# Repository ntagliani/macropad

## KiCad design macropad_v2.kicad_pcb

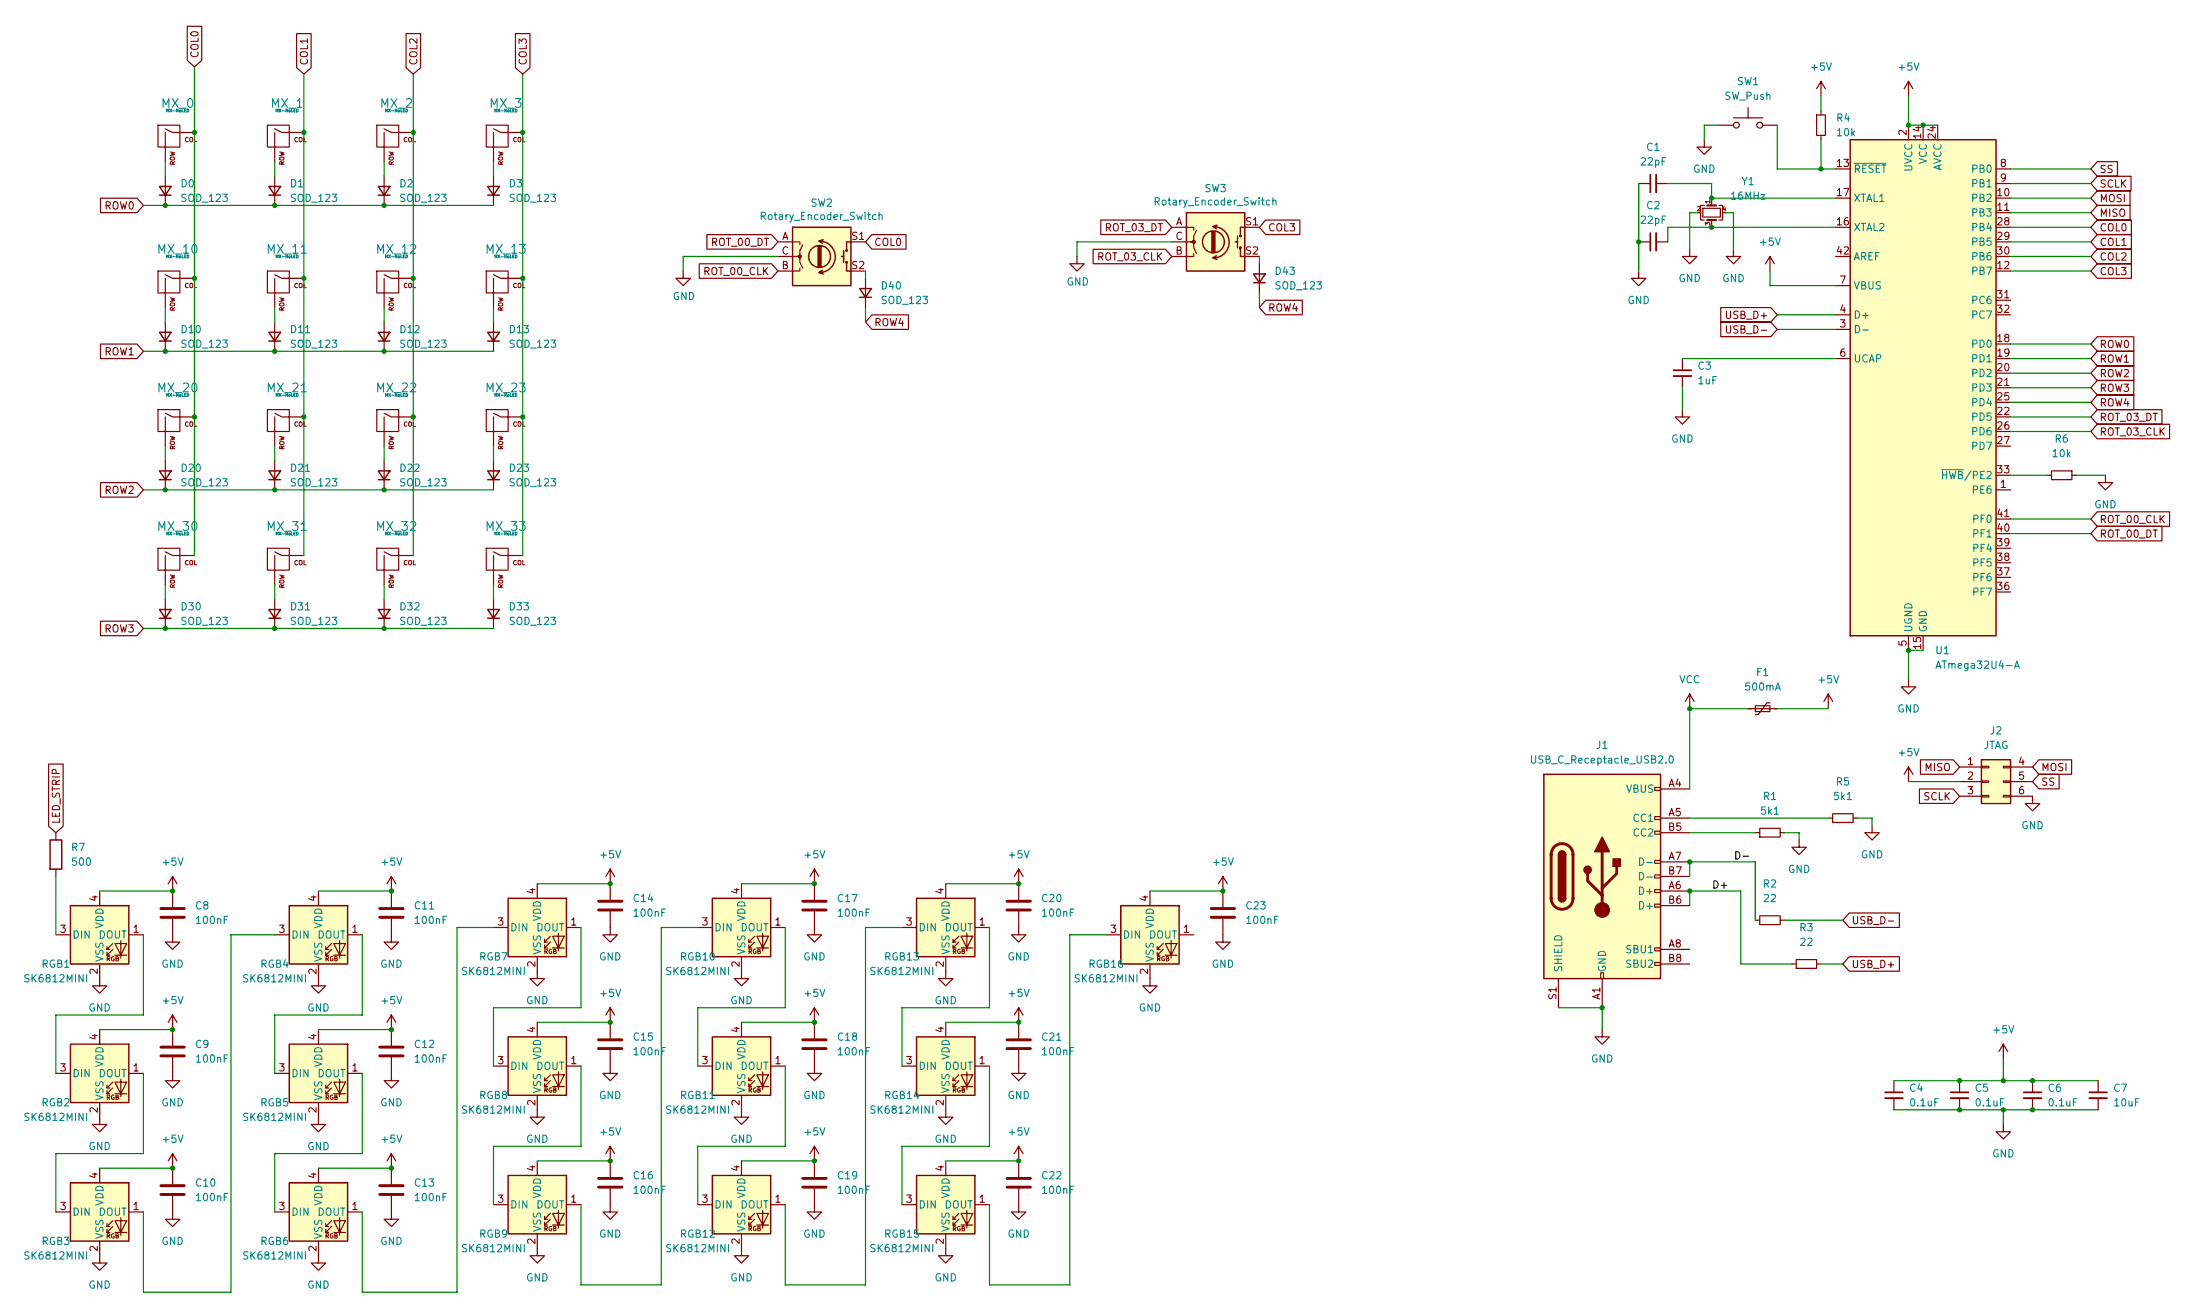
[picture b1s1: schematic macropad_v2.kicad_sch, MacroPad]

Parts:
C1, C2: 22pF; C_0805_2012Metric
C3: 1uF; C_0805_2012Metric
C4, C5, C6: 0.1uF; C_0805_2012Metric
C7: 10uF; C_0805_2012Metric
C8, C9, C10, C11, C12, C13, C14, C15, C16, C17, C18, C19, C20, C21, C22, C23: 100nF; C_0805_2012Metric
D0, D1, D2, D3, D10, D11, D12, D13, D20, D21, D22, D23, D30, D31, D32, D33, D40, D43: SOD_123; D_0805_2012Metric
F1: 500mA; Fuse_0805_2012Metric
J1: USB_C_Receptacle_USB2.0; USB_C_Receptacle_HRO_TYPE-C-31-M-12
J2: JTAG; Reset_Pretty
MX_0, MX_1, MX_2, MX_3, MX_10, MX_11, MX_12, MX_13, MX_20, MX_21, MX_22, MX_23, MX_30, MX_31, MX_32, MX_33: MX-NoLED; SW_Cherry_MX_1.00u_Plate
R1, R5: 5k1; R_0805_2012Metric
R2, R3: 22; R_0805_2012Metric
R4, R6: 10k; R_0805_2012Metric
R7: 500; R_0805_2012Metric
RGB1, RGB2, RGB3, RGB4, RGB5, RGB6, RGB7, RGB8, RGB9, RGB10, RGB11, RGB12, RGB13, RGB14, RGB15, RGB16: SK6812MINI; LED_SK6812MINI_PLCC4_3.5x3.5mm_P1.75mm
SW1: SW_Push; Reset_Pretty
SW2, SW3: Rotary_Encoder_Switch; RotaryEncoder_Alps_EC11E-Switch_Vertical_H20mm
U1: ATmega32U4-A; TQFP-44_10x10mm_P0.8mm
Y1: 16MHz; Crystal_SMD_3225-4Pin_3.2x2.5mm

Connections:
+5V: C4.1, C5.1, C6.1, C7.1, C8.1, C9.1, C10.1, C11.1, C12.1, C13.1, C14.1, C15.1, C16.1, C17.1, C18.1, C19.1, C20.1, C21.1, C22.1, C23.1, F1.2, J2.2, R4.1, RGB1.4 (VDD), RGB2.4 (VDD), RGB3.4 (VDD), RGB4.4 (VDD), RGB5.4 (VDD), RGB6.4 (VDD), RGB7.4 (VDD), RGB8.4 (VDD), RGB9.4 (VDD), RGB10.4 (VDD), RGB11.4 (VDD), RGB12.4 (VDD), RGB13.4 (VDD), RGB14.4 (VDD), RGB15.4 (VDD), RGB16.4 (VDD), U1.2 (UVCC), U1.7 (VBUS), U1.14 (VCC), U1.24 (AVCC), U1.34 (VCC), U1.44 (AVCC)
/D+: J1.A6 (D+), J1.B6 (D+), R3.1
/D-: J1.A7 (D-), J1.B7 (D-), R2.1
COL0: MX_0.1 (COL), MX_10.1 (COL), MX_20.1 (COL), MX_30.1 (COL), SW2.S1, U1.28 (PB4)
COL1: MX_1.1 (COL), MX_11.1 (COL), MX_21.1 (COL), MX_31.1 (COL), U1.29 (PB5)
COL2: MX_2.1 (COL), MX_12.1 (COL), MX_22.1 (COL), MX_32.1 (COL), U1.30 (PB6)
COL3: MX_3.1 (COL), MX_13.1 (COL), MX_23.1 (COL), MX_33.1 (COL), SW3.S1, U1.12 (PB7)
GND: C1.1, C2.1, C3.2, C4.2, C5.2, C6.2, C7.2, C8.2, C9.2, C10.2, C11.2, C12.2, C13.2, C14.2, C15.2, C16.2, C17.2, C18.2, C19.2, C20.2, C21.2, C22.2, C23.2, J1.A1 (GND), J1.A12 (GND), J1.B1 (GND), J1.B12 (GND), J1.S1 (SHIELD), J2.6, R1.2, R5.2, R6.1, RGB1.2 (VSS), RGB2.2 (VSS), RGB3.2 (VSS), RGB4.2 (VSS), RGB5.2 (VSS), RGB6.2 (VSS), RGB7.2 (VSS), RGB8.2 (VSS), RGB9.2 (VSS), RGB10.2 (VSS), RGB11.2 (VSS), RGB12.2 (VSS), RGB13.2 (VSS), RGB14.2 (VSS), RGB15.2 (VSS), RGB16.2 (VSS), SW1.1, SW2.C, SW3.C, U1.5 (UGND), U1.15 (GND), U1.23 (GND), U1.35 (GND), U1.43 (GND), Y1.2, Y1.4
LED_STRIP: R7.1
MISO: J2.1, U1.11 (PB3)
MOSI: J2.4, U1.10 (PB2)
unnamed: C1.2, U1.17 (XTAL1), Y1.1
unnamed: C2.2, U1.16 (XTAL2), Y1.3
unnamed: C3.1, U1.6 (UCAP)
unnamed: D0.2 (A), MX_0.2 (ROW)
unnamed: D1.2 (A), MX_1.2 (ROW)
unnamed: D2.2 (A), MX_2.2 (ROW)
unnamed: D3.2 (A), MX_3.2 (ROW)
unnamed: D10.2 (A), MX_10.2 (ROW)
unnamed: D11.2 (A), MX_11.2 (ROW)
unnamed: D12.2 (A), MX_12.2 (ROW)
unnamed: D13.2 (A), MX_13.2 (ROW)
unnamed: D20.2 (A), MX_20.2 (ROW)
unnamed: D21.2 (A), MX_21.2 (ROW)
unnamed: D22.2 (A), MX_22.2 (ROW)
unnamed: D23.2 (A), MX_23.2 (ROW)
unnamed: D30.2 (A), MX_30.2 (ROW)
unnamed: D31.2 (A), MX_31.2 (ROW)
unnamed: D32.2 (A), MX_32.2 (ROW)
unnamed: D33.2 (A), MX_33.2 (ROW)
unnamed: J1.A5 (CC1), R5.1
unnamed: J1.B5 (CC2), R1.1
unnamed: R4.2, SW1.2, U1.13 (~RESET)
unnamed: R6.2, U1.33 (~HWB/PE2)
unnamed: R7.2, RGB1.3 (DIN)
unnamed: RGB1.1 (DOUT), RGB2.3 (DIN)
unnamed: RGB2.1 (DOUT), RGB3.3 (DIN)
unnamed: RGB3.1 (DOUT), RGB4.3 (DIN)
unnamed: RGB4.1 (DOUT), RGB5.3 (DIN)
unnamed: RGB5.1 (DOUT), RGB6.3 (DIN)
unnamed: RGB6.1 (DOUT), RGB7.3 (DIN)
unnamed: RGB7.1 (DOUT), RGB8.3 (DIN)
unnamed: RGB8.1 (DOUT), RGB9.3 (DIN)
unnamed: RGB10.1 (DOUT), RGB11.3 (DIN)
unnamed: RGB9.1 (DOUT), RGB10.3 (DIN)
unnamed: RGB11.1 (DOUT), RGB12.3 (DIN)
unnamed: RGB12.1 (DOUT), RGB13.3 (DIN)
unnamed: RGB13.1 (DOUT), RGB14.3 (DIN)
unnamed: RGB14.1 (DOUT), RGB15.3 (DIN)
unnamed: RGB15.1 (DOUT), RGB16.3 (DIN)
unnamed: D40.2 (A), SW2.S2
unnamed: D43.2 (A), SW3.S2
ROT_00_CLK: SW2.B, U1.41 (PF0)
ROT_00_DT: SW2.A, U1.40 (PF1)
ROT_03_CLK: SW3.B, U1.26 (PD6)
ROT_03_DT: SW3.A, U1.22 (PD5)
ROW0: D0.1 (K), D1.1 (K), D2.1 (K), D3.1 (K), U1.18 (PD0)
ROW1: D10.1 (K), D11.1 (K), D12.1 (K), D13.1 (K), U1.19 (PD1)
ROW2: D20.1 (K), D21.1 (K), D22.1 (K), D23.1 (K), U1.20 (PD2)
ROW3: D30.1 (K), D31.1 (K), D32.1 (K), D33.1 (K), U1.21 (PD3)
ROW4: D40.1 (K), D43.1 (K), U1.25 (PD4)
SCLK: J2.3, U1.9 (PB1)
SS: J2.5, U1.8 (PB0)
USB_D+: R3.2, U1.4 (D+)
USB_D-: R2.2, U1.3 (D-)
VCC: F1.1, J1.A4 (VBUS), J1.A9 (VBUS), J1.B4 (VBUS), J1.B9 (VBUS)

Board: 2 copper layers, 88 parts (68 on the bottom side), 65 nets, no tracks yet.

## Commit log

2022-09-26 Initial setup of the repository and submodule connection
2022-09-26 Kicad project initial setup
2023-04-04 added submodule
2023-04-27 Added schematics files to project
2023-04-27 Added license file
